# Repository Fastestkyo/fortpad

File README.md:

# fortpad
a hackpad for sweating in fortnite. this has 16 keys and a oled display.

This is a hackpad which has 1,2,3,4,5, tab, q,w,e,r,a,s,d,ctrl,alt and space, which are my keybinds for fortnite.
the hard part for this was the pcb since this is the 2nd pcb ive made. the matrix thing for this is 4x4.
the pcb is 100x100 mm and the case is 130x130x30 mm

## BOM:
| item                            | amt|
|---------------------------------|----|
| switches                        | 16 |
| Seeed XIAO RP2040               | 1  |
| 1N4148 Diodes                   | 16 |
| 0.91 inch OLED Display          | 1  |
| Blank DSA Keycaps (White)       | 16 |
| M3x16mm Screws                  | 10 |
| M3x5mmx4mm Heatset Inserts      | 4  |

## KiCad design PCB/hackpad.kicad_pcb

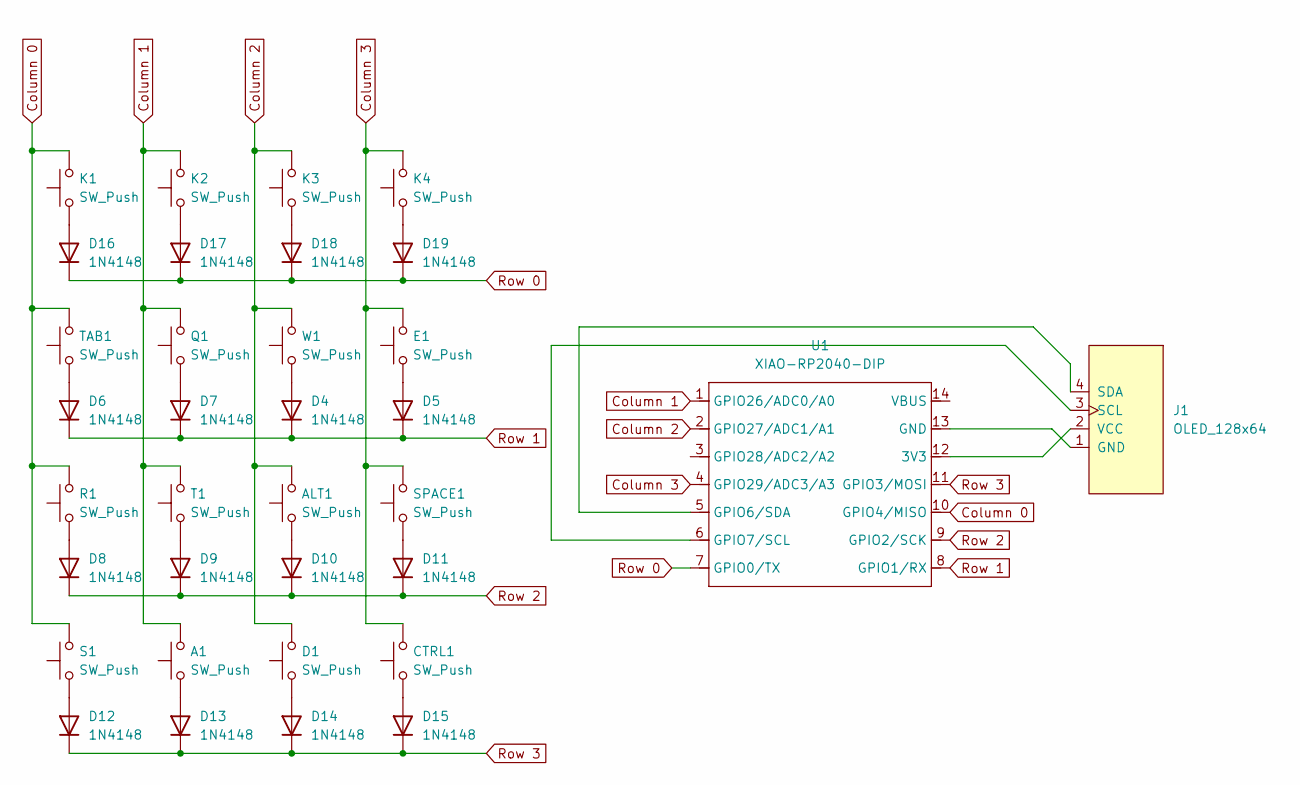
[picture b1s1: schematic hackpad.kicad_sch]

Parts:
A1: SW_Push; SW_Cherry_MX_1.00u_PCB
ALT1: SW_Push; SW_Cherry_MX_1.00u_PCB
CTRL1: SW_Push; SW_Cherry_MX_1.00u_PCB
D1: SW_Push; SW_Cherry_MX_1.00u_PCB
D4, D5, D6, D7, D8, D9, D10, D11, D12, D13, D14, D15, D16, D17, D18, D19: 1N4148; D_DO-35_SOD27_P7.62mm_Horizontal
E1: SW_Push; SW_Cherry_MX_1.00u_PCB
J1: OLED_128x64
K1, K2, K3, K4: SW_Push; SW_Cherry_MX_1.00u_PCB
Q1: SW_Push; SW_Cherry_MX_1.00u_PCB
R1: SW_Push; SW_Cherry_MX_1.00u_PCB
S1: SW_Push; SW_Cherry_MX_1.00u_PCB
SPACE1: SW_Push; SW_Cherry_MX_1.00u_PCB
T1: SW_Push; SW_Cherry_MX_1.00u_PCB
TAB1: SW_Push; SW_Cherry_MX_1.00u_PCB
U1: XIAO-RP2040-DIP
W1: SW_Push; SW_Cherry_MX_1.00u_PCB

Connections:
Column 0: K1.2, R1.2, S1.2, TAB1.2, U1.10 (GPIO4/MISO)
Column 1: A1.2, K2.2, Q1.2, T1.2, U1.1 (GPIO26/ADC0/A0)
Column 2: ALT1.2, D1.2, K3.2, U1.2 (GPIO27/ADC1/A1), W1.2
Column 3: CTRL1.2, E1.2, K4.2, SPACE1.2, U1.4 (GPIO29/ADC3/A3)
unnamed: D4.2 (A), W1.1
unnamed: D5.2 (A), E1.1
unnamed: D6.2 (A), TAB1.1
unnamed: D7.2 (A), Q1.1
unnamed: D8.2 (A), R1.1
unnamed: D9.2 (A), T1.1
unnamed: ALT1.1, D10.2 (A)
unnamed: D11.2 (A), SPACE1.1
unnamed: D12.2 (A), S1.1
unnamed: A1.1, D13.2 (A)
unnamed: D1.1, D14.2 (A)
unnamed: CTRL1.1, D15.2 (A)
unnamed: D16.2 (A), K1.1
unnamed: D17.2 (A), K2.1
unnamed: D18.2 (A), K3.1
unnamed: D19.2 (A), K4.1
unnamed: J1.1 (GND), U1.13 (GND)
unnamed: J1.3 (SCL), U1.6 (GPIO7/SCL)
unnamed: J1.4 (SDA), U1.5 (GPIO6/SDA)
unnamed: J1.2 (VCC), U1.12 (3V3)
Row 0: D16.1 (K), D17.1 (K), D18.1 (K), D19.1 (K), U1.7 (GPIO0/TX)
Row 1: D4.1 (K), D5.1 (K), D6.1 (K), D7.1 (K), U1.8 (GPIO1/RX)
Row 2: D8.1 (K), D9.1 (K), D10.1 (K), D11.1 (K), U1.9 (GPIO2/SCK)
Row 3: D12.1 (K), D13.1 (K), D14.1 (K), D15.1 (K), U1.11 (GPIO3/MOSI)

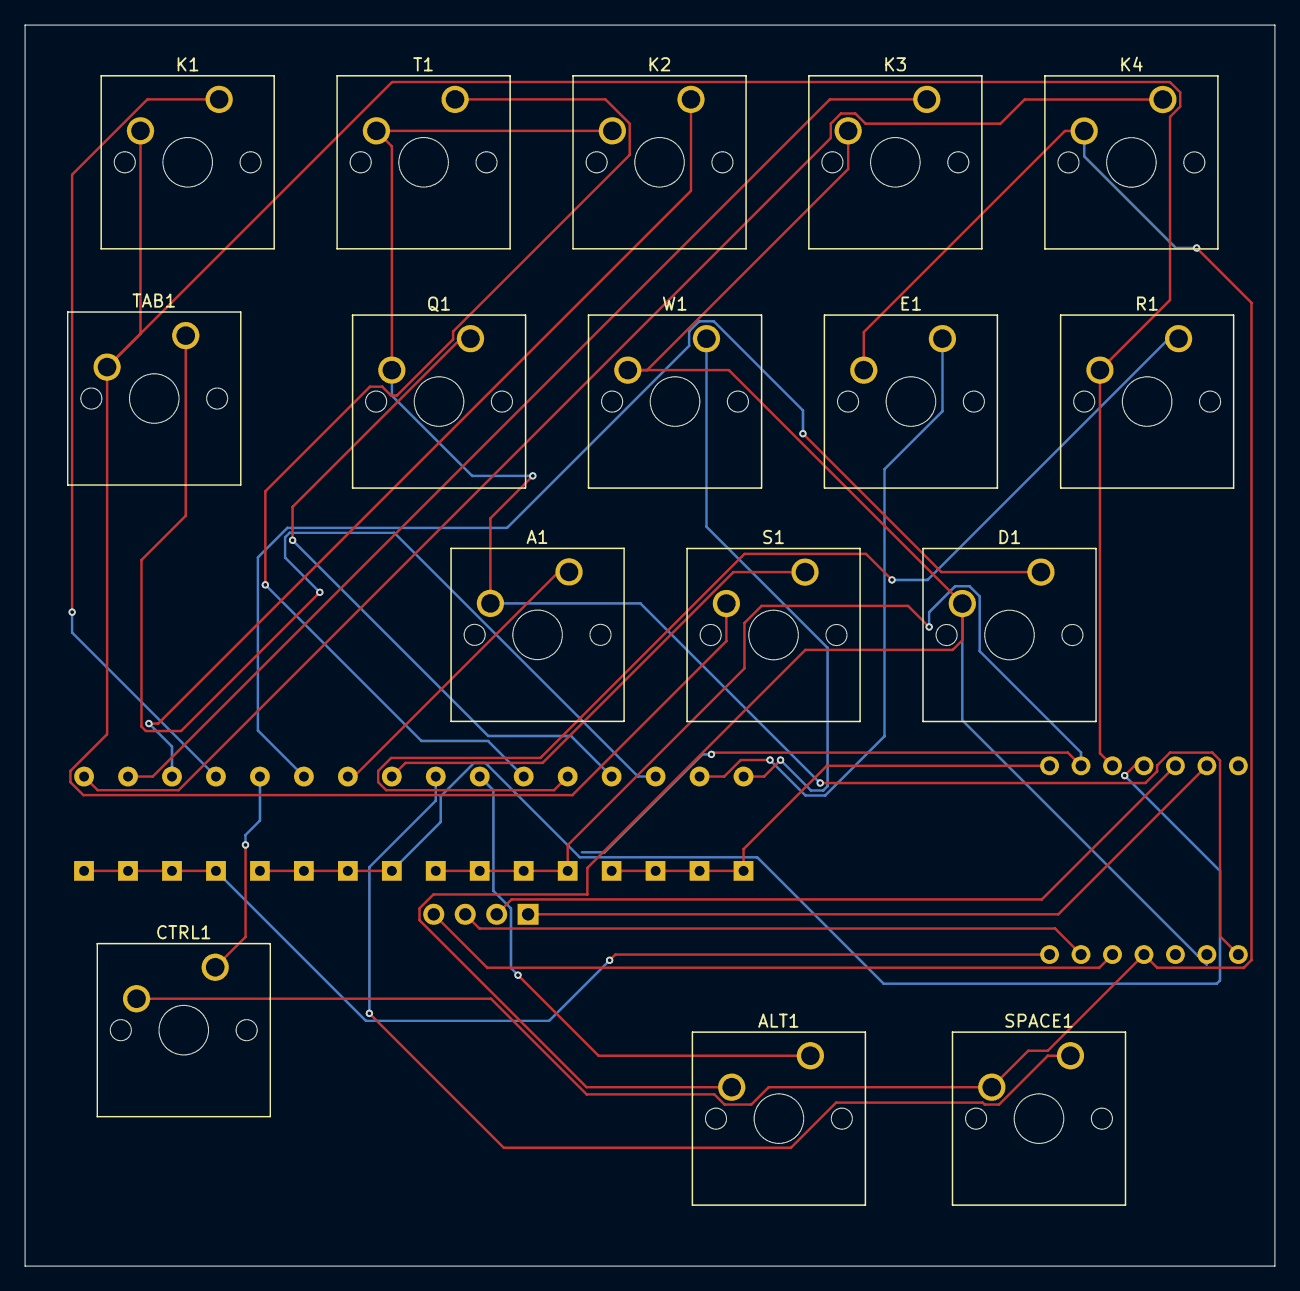
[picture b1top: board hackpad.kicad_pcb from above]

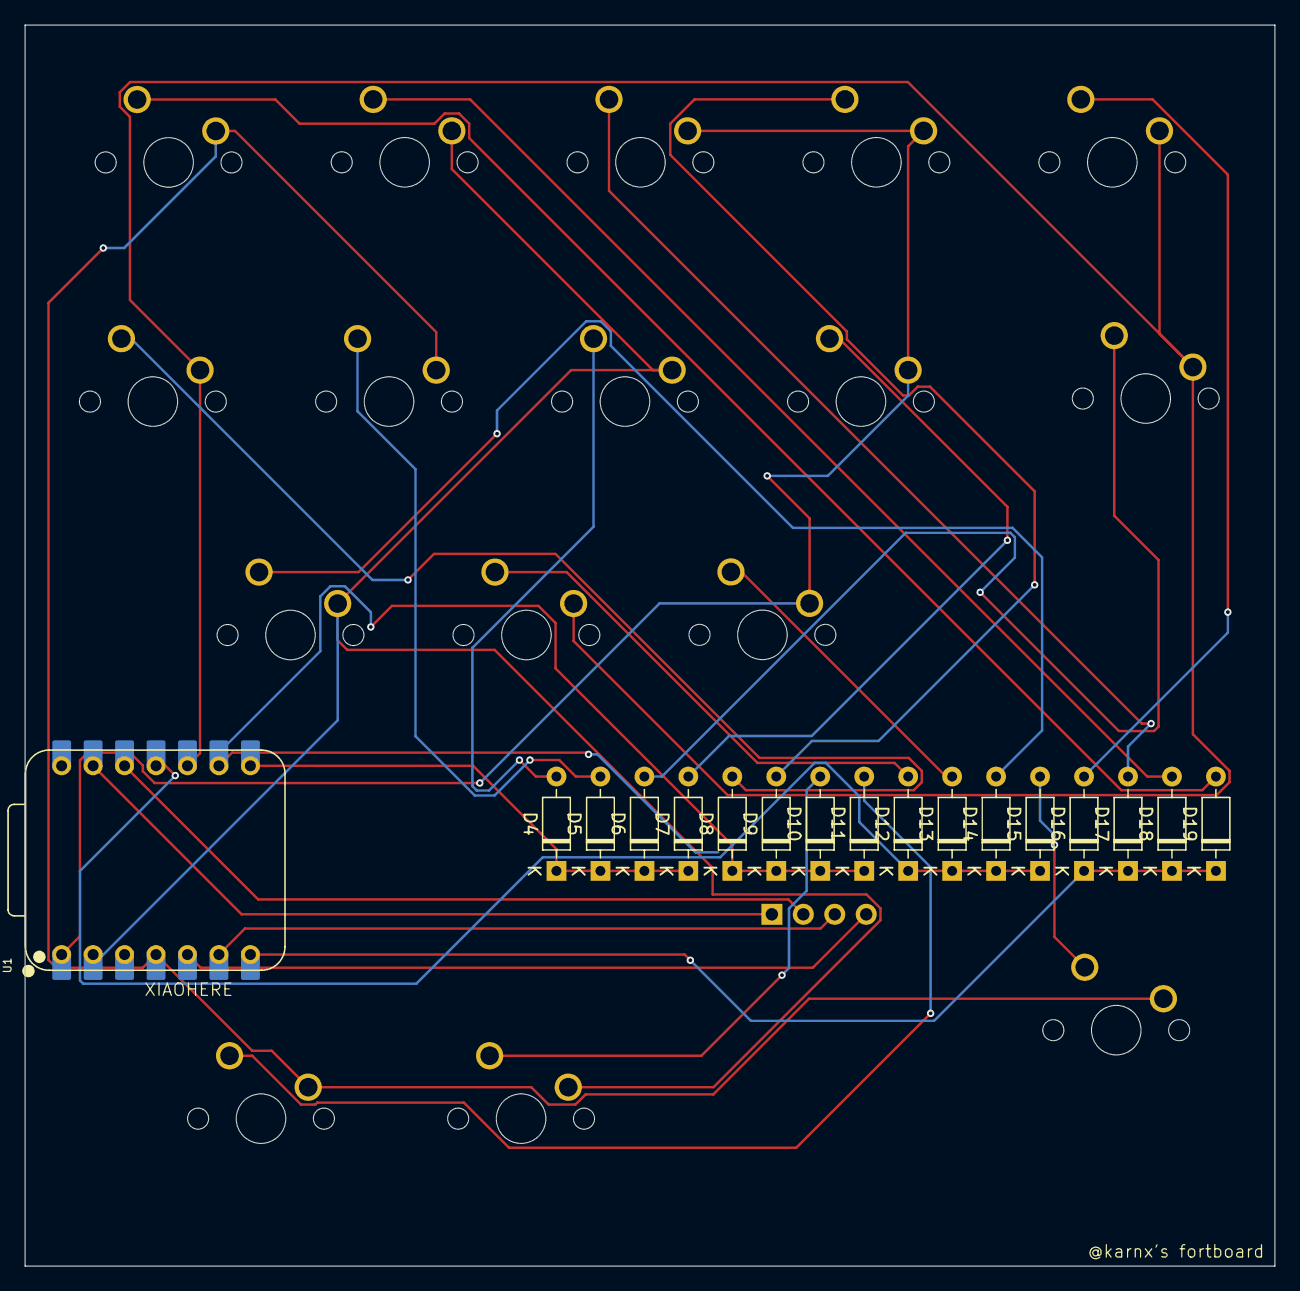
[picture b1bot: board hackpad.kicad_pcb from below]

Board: 2 copper layers, 100.9 x 100.2 mm, 34 parts (18 on the bottom side), 28 nets.

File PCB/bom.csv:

Designator,Footprint,Quantity,Value,LCSC Part #
"A1, ALT1, CTRL1, D1, E1, K1, K2, K3, K4, Q1, R1, S1, SPACE1, T1, TAB1, W1",SW_Cherry_MX_1.00u_PCB,16,SW_Push,
"D10, D11, D12, D13, D14, D15, D16, D17, D18, D19, D4, D5, D6, D7, D8, D9",D_DO-35_SOD27_P7.62mm_Horizontal,16,1N4148,
J1,OLED_128x64,1,OLED_128x64,
U1,XIAO-RP2040-DIP,1,XIAO-RP2040-DIP,

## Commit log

2025-06-06 Asdasd
2025-06-07 adsad
